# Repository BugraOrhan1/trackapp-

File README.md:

# 📡 TrackApp - RF Signal Scanner
## Eigen gebouwde Target Blue Eye alternatief
### Versie 2.0 - Juni 2026

---

## WAT IS DIT?

TrackApp is een zelfgebouwde RF (Radio Frequentie) scanner.
Hij scant het frequentiebereik 380-400 MHz.
Dat is de band waar in Nederland C2000 hulpdiensten op werken.

De scanner meet ALLEEN de signaalsterkte.
Hij decodeert NIETS - hij luistert niet mee naar gesprekken.

Op basis van de sterkte gaan LED lampjes branden.
Hoe sterker het signaal, hoe meer LEDs er branden.

Het systeem heeft een Smart Analyzer die leert welke
signalen van vaste masten komen. Die worden genegeerd.
Alleen nieuwe/wisselende signalen activeren de LEDs.

---

## HARDWARE

| Onderdeel | Type |
|-----------|------|
| Computer | Raspberry Pi Zero 2 W |
| Radio | RTL-SDR 2832 USB dongle |
| LEDs | 4x (groen/geel/oranje/rood) |
| Weerstanden | 4x 330 Ohm |
| SD kaart | 32GB Class 10 |

---

## BEDRADING

### GPIO Pin Schema (BCM)
GPIO 17 ──[330Ω]──[🟢 GROEN ]──GND
GPIO 27 ──[330Ω]──[🟡 GEEL ]──GND
GPIO 22 ──[330Ω]──[🟠 ORANJE]──GND
GPIO 23 ──[330Ω]──[🔴 ROOD ]──GND
USB ──── [RTL-SDR Dongle] ──── [Antenne]

text

### Pin Tabel

| LED | Kleur | GPIO | Fysieke Pin |
|-----|-------|------|-------------|
| Groen | 🟢 | 17 | 11 |
| Geel | 🟡 | 27 | 13 |
| Oranje | 🟠 | 22 | 15 |
| Rood | 🔴 | 23 | 16 |

---

## INSTALLATIE

### Stap 1: Raspberry Pi OS

Gebruik Raspberry Pi Imager:
- OS: Raspberry Pi OS Lite (64-bit)
- Hostname: test
- Username: test
- Enable SSH
- WiFi configureren

### Stap 2: SSH naar Pi

```bash
ssh test@test.local
Stap 3: Code downloaden
Bash

cd ~
sudo apt update
sudo apt install -y git
git clone https://github.com/BugraOrhan1/trackapp-.git
cd trackapp-/TrackApp/raspberry-pi
chmod +x install.sh
sudo ./install.sh
Stap 4: Fixes
Bash

# pyrtlsdr downgrade
sudo /opt/tetra-scanner/venv/bin/pip uninstall pyrtlsdr -y
sudo /opt/tetra-scanner/venv/bin/pip install pyrtlsdr==0.3.0

# pkg_resources patch
RTLSDR_INIT=$(find /opt/tetra-scanner/venv -name "__init__.py" -path "*/rtlsdr/*" | head -1)
sudo sed -i 's|^import pkg_resources|try:\n    import pkg_resources\nexcept ImportError:\n    import importlib.metadata as pkg_resources|' "$RTLSDR_INIT"
Stap 5: Kalibreren
Bash

sudo systemctl stop tetra-scanner
cd /opt/tetra-scanner
sudo venv/bin/python3 calibrate.py
# Pas drempels aan in config.py met de aanbevolen waarden
sudo systemctl start tetra-scanner
Stap 6: Reboot
Bash

sudo reboot
LED GEDRAG
Normaal
LED Status	Betekenis
Groen knippert kort (elke 3 sec)	Systeem leeft, geen signaal
Alles uit	Scanner gestopt of crashed
Groen vast aan	Zwak mobiel signaal
Groen + Geel	Middelmatig signaal
Groen + Geel + Oranje	Sterk signaal
Groen + Geel + Oranje + Rood	Zeer sterk signaal
Alle 4 flashen	BURST detectie
Pulserend	BEWEGING detectie
Opstart
Wat je ziet	Betekenis
Knight Rider effect	Scanner start op
2x groen knippert	Opstart compleet
Rood knippert 5x	Init fout
Rood knippert 10x	RTL-SDR niet gevonden
Foutdiagnose
Symptoom	Probleem	Oplossing
Geen heartbeat	Scanner crashed	Reboot
Rood blijft knipperen	RTL-SDR fout	Check USB
Alle LEDs altijd aan	Drempels te laag	Kalibreer
Geen LEDs ooit aan	Drempels te hoog	Kalibreer
LEDs flikkeren snel	Gain probleem	Check config
SMART ANALYZER
Hoe werkt het
Eerste 20 scans = leerperiode.
Daarna: slim filteren actief.

Detectie Types
Type	Wat
MAST	Vast basisstation (genegeerd)
MOBIEL	Wisselend signaal
BURST	Plotseling signaal
BEWEGING	Naderend signaal
Strike Systeem
7 stabiele metingen → MAST
Wisselende metingen → strikes omlaag
0 strikes → weer MOBIEL
LED Drempels (Smart mode)
dB	LED
28+	🟢 Groen
38+	🟡 + Geel
48+	🟠 + Oranje
60+	🔴 + Rood
BESTANDEN
text

/opt/tetra-scanner/
├── scanner.py          ← Hoofdprogramma
├── config.py           ← Instellingen
├── signal_analyzer.py  ← RTL-SDR + FFT
├── smart_analyzer.py   ← Slim brein
├── led_controller.py   ← LED + heartbeat
├── web.py              ← Webpagina
├── calibrate.py        ← Kalibratie tool
├── data/               ← CSV + masten
├── logs/               ← Log bestanden
└── venv/               ← Python env
SERVICES
Service	Functie
tetra-scanner	De scanner
trackapp-web	Webpagina
wifi-dual	Hotspot + WiFi
tetra-health.timer	Health check (60s)
watchdog	Hardware watchdog
tailscaled	Tailscale VPN
Commando's
Bash

# Status
sudo systemctl status tetra-scanner

# Logs
sudo journalctl -u tetra-scanner -f

# Restart
sudo systemctl restart tetra-scanner

# Stop
sudo systemctl stop tetra-scanner
WIFI EN HOTSPOT
Dual Mode
Pi maakt twee interfaces:

wlan0 = thuis WiFi (internet)
uap0 = TrackApp hotspot
Beide werken tegelijk.

TrackApp Hotspot
Setting	Value
SSID	TrackApp
Password	TrackApp2026
IP	192.168.50.1
Channel	6
Webpagina
Thuis: http://test.local:8080
Hotspot: http://192.168.50.1:8080
Tailscale: http://100.107.246.20:8080
TAILSCALE
Bash

# Setup eenmalig
sudo tailscale up --ssh

# IP opvragen
tailscale ip -4

# Status
tailscale status
Werkt alleen met internet.

HANDIGE COMMANDO'S
Logs bekijken
Bash

sudo journalctl -u tetra-scanner -f
sudo journalctl -u tetra-scanner -n 50
sudo journalctl -u tetra-scanner --since '30 min ago'
Drempels aanpassen
Bash

sudo sed -i 's/^THRESHOLD_GREEN.*=.*/THRESHOLD_GREEN = 47.2/' /opt/tetra-scanner/config.py
sudo systemctl restart tetra-scanner
Handmatig testen
Bash

sudo systemctl stop tetra-scanner
cd /opt/tetra-scanner
sudo env TERM=xterm ./venv/bin/python3 scanner.py
# Ctrl+C om te stoppen
sudo systemctl start tetra-scanner
CSV data bekijken
Bash

ls -t /opt/tetra-scanner/data/signal_data_*.csv | head -5
tail -20 $(ls -t /opt/tetra-scanner/data/signal_data_*.csv | head -1)
Bekende masten
Bash

cat /opt/tetra-scanner/data/known_masts.json
WiFi checks
Bash

iwgetid -r
ip -4 addr show
sudo iw dev uap0 station dump
Updates naar GitHub
Bash

cd ~/trackapp-/TrackApp/raspberry-pi
sudo cp /opt/tetra-scanner/*.py .
sudo chown -R test:test .
cd ~/trackapp-
git add .
git commit -m "Update: beschrijving"
git push
PROBLEMEN OPLOSSEN
Scanner start niet
Bash

sudo systemctl status tetra-scanner
sudo journalctl -u tetra-scanner -n 50
sudo systemctl restart tetra-scanner
RTL-SDR niet gevonden
Bash

lsusb | grep -i rtl
sudo reboot
pyrtlsdr error
Bash

/opt/tetra-scanner/venv/bin/python3 -c "import rtlsdr; print('OK')"
sudo /opt/tetra-scanner/venv/bin/pip install pyrtlsdr==0.3.0
Alle LEDs branden
Oorzaak: drempels te laag. Kalibreer opnieuw.

Geen LEDs ooit aan
Oorzaak: drempels te hoog OF geen signaal. Test met:

Bash

sudo systemctl stop tetra-scanner
python3 << 'TESTEOF'
import RPi.GPIO as GPIO
import time
GPIO.setmode(GPIO.BCM)
for pin in [17, 27, 22, 23]:
    GPIO.setup(pin, GPIO.OUT)
    GPIO.output(pin, GPIO.HIGH)
    time.sleep(1)
    GPIO.output(pin, GPIO.LOW)
GPIO.cleanup()
TESTEOF
sudo systemctl start tetra-scanner
Pi reageert niet
Wacht 2 minuten (watchdog herstart)
Stroom eraf, 10 sec wachten, weer erop
Als niets: SD kaart check
SD vol
Bash

df -h
sudo rm /opt/tetra-scanner/data/signal_data_2026050*.csv
sudo journalctl --vacuum-time=3d
TECHNISCHE DETAILS
Scan instellingen
Bereik: 380-400 MHz
Stap: 25 kHz
Frequenties: 801
Sample rate: 1.024 MHz
Samples: 65536
Smart Analyzer
Parameter	Waarde
Stable strikes nodig	7
Max strikes	25
History length	60
Std stable threshold	2.5 dB
Movement threshold	4.0 dB
Location overlap	30%
Learning scans	20
LED Drempels Smart Mode
text

28+ dB → Groen
38+ dB → Geel
48+ dB → Oranje
60+ dB → Rood
CONFIG.PY INSTELLINGEN
Python

FREQ_START_MHZ = 380.0
FREQ_END_MHZ = 400.0
FREQ_STEP_MHZ = 0.025
SAMPLE_RATE = 1024000
GAIN = 35.0
PPM_CORRECTION = 0

LED_GREEN = 17
LED_YELLOW = 27
LED_ORANGE = 22
LED_RED = 23

THRESHOLD_GREEN = 47.2
THRESHOLD_YELLOW = 53.2
THRESHOLD_ORANGE = 61.2
THRESHOLD_RED = 71.2

SCAN_INTERVAL = 0.5
SHOW_TERMINAL_OUTPUT = False
LOG_LEVEL = "INFO"
GEBRUIK IN DE AUTO
Setup
Pi op 5V USB lader
RTL-SDR in USB DATA poort
Antenne opzetten
2-3 minuten wachten
Wat je ziet
Knight Rider = opstarten
2x groen flash = klaar
Groen knippert = alles werkt
LEDs branden = actief signaal
Tips
Antenne: externe magneetvoet op dak = 10x beter
Positie: niet achter metaal
Kalibreer op locatie waar je het meest bent
Gain 35 dB is meestal goed
Stroom: goede 5V voeding
LOKALE WIJZIGINGEN LOG
#	Wijziging	Bestand
1	Vaste Gain (35.0)	config.py
2	PPM correctie fix	signal_analyzer.py
3	pyrtlsdr 0.3.0	venv
4	pkg_resources patch	rtlsdr/init.py
5	Smart Analyzer v3.0	smart_analyzer.py
6	Ultra LED Controller	led_controller.py
7	Dual Mode WiFi	wifi-dual.sh
8	Web Interface	web.py
9	Health Check	tetra-health
10	Hardware Watchdog	/etc/watchdog.conf
11	Tailscale	systeem
12	Drempels gekalibreerd	config.py
13	DVB-T blacklist	modprobe.d
14	GPIO pinnen	config.py
VERSIE INFO
Versie: 2.0
Datum: Juni 2026
Maker: BugraOrhan1
Hardware: Raspberry Pi Zero 2 W + RTL-SDR 2832
OS: Raspberry Pi OS Debian Trixie 64-bit
Python: 3.13
JURIDISCHE WAARSCHUWING
Het afluisteren van hulpdiensten (C2000/TETRA) is in
Nederland illegaal volgens de Telecommunicatiewet
(Art. 139c Wetboek van Strafrecht).

Dit project is ALLEEN voor educatieve doeleinden.
Het meet ALLEEN signaalsterkte.
Het decodeert GEEN communicatie.
Het luistert NIET mee met gesprekken.

Gebruik conform lokale wetgeving.
De maker is niet verantwoordelijk voor misbruik.

LINKS
Repository: https://github.com/BugraOrhan1/trackapp-
Raspberry Pi Imager: https://www.raspberrypi.com/software/
Win32 Disk Imager: https://sourceforge.net/projects/win32diskimager/
Tailscale: https://tailscale.com
RTL-SDR: https://www.rtl-sdr.com
EINDE README

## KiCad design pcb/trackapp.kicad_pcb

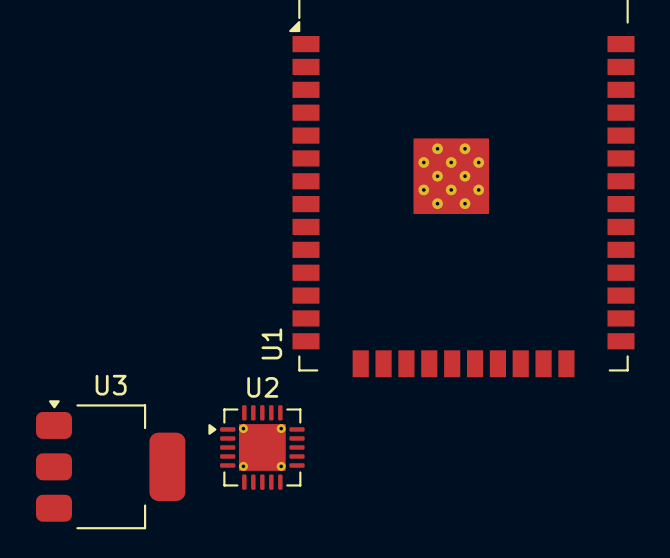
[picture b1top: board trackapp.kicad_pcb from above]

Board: 2 copper layers, 3 parts (0 on the bottom side), 2 nets, no tracks yet.

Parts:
U1: ESP32-WROOM-32
U2: Si4463; QFN-20-1EP_4x4mm_P0.5mm_EP2.6x2.6mm_ThermalVias
U3: AMS1117-3.3; SOT-223-3_TabPin2

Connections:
unnamed: U1.1 (GND), U1.15 (GND), U1.38 (GND), U1.39 (GND)
unnamed: U2.18 (GND), U2.21 (GND)

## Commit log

2026-03-23 first upload raspberry scanner + web app
2026-03-23 Auto Bluetooth paired-device connect and reconnect
2026-03-23 Fix netlify.toml paths for deployment
2026-03-23 Add environment variables template
2026-03-23 Add Neon database setup and verification guide
2026-03-23 Add complete .env template and SQL schema ready to paste
2026-03-23 Improve JWT_SECRET documentation with security requirements
2026-03-23 Fix deprecated mobile-web-app meta tag
2026-03-23 Add detailed error logging and health check endpoint
2026-03-23 TEMP: Disable authentication - demo mode enabled
2026-03-23 Add comprehensive Raspberry Pi Bluetooth communication setup guide
2026-03-23 Fix bluetoothctl pairing commands - clarify interactive menu vs terminal
2026-03-23 Add quick-start scripts for easy project setup
2026-03-23 Add all-in-one Raspberry Pi setup script
2026-03-23 Fix setuptools version from 81.0.2 to 80.10.2 (81.0.2 doesn't exist)
2026-03-24 Improve reliability: configurable auth mode, safer API requests, hardened Pi setup
2026-03-25 Repo cleanup: merge docs, remove redundant files, simplify run workflow
2026-03-25 Add temporary local API/database mode to run without Netlify
2026-03-25 Tune scanner: adaptive background EMA and explicit green level
2026-03-25 Fix scanner default run: fallback argparse defaults for systemd startup
2026-03-25 Fix Bluetooth auto-bind for new bluetoothctl syntax
2026-03-25 Fix rfcomm lifecycle: bind as root in systemd and persist BT target MAC
2026-03-25 Improve drive-by detection and add pre-alert diagnostics
2026-03-26 BLE + webapp RF orb realtime scaling and decay
2026-03-26 Add iOS cloud build path and signal-mode BLE app updates
2026-03-26 Fix iOS cloud workflow cache and artifact paths
2026-03-26 Harden setup-node cache path for iOS workflow
2026-03-26 Add TypeScript for Capacitor TS config in iOS CI
2026-03-26 Fix Capacitor webDir and CI web asset sync for iOS build
2026-03-26 Add optional TestFlight upload flow and docs
2026-03-30 backup
2026-03-31 TrackApp BLE: eerste commit na opschoning
2026-04-03 TrackApp: BLE JSON flow + RTL scanner + webapp sync + README updates
2026-04-03 Restructure TrackApp into four app folders
2026-04-03 page fix
2026-04-03 Fix GitHub Pages deployment via gh-pages branch
2026-04-03 Remove Node20 gh-pages action from deploy workflow
2026-04-03 0.0.91
2026-04-03 0.0.92
2026-04-03 0.0.93
2026-04-03 Deploy webapp to GitHub Pages
2026-04-06 Show app directly without login
2026-04-06 Start app directly without login
2026-04-06 Clarify Pi BLE unsupported on iPhone browsers
2026-04-10 update for beta
2026-04-10 beta update v1.1
2026-04-10 beta v3
2026-04-10 beta v4
2026-04-10 beta v4.1
2026-04-10 beta v 5
2026-04-10 Add iOS IPA GitHub Actions workflow
2026-04-10 Move iOS workflow to repo root
2026-04-10 Harden iOS workflow secret checks
2026-04-10 Use production environment for iOS workflow
2026-04-10 Use TrackApp environment for iOS workflow
2026-04-10 Fix EAS config validation
2026-04-10 Link EAS project and enable remote versioning
2026-04-13 Fix iOS build plist and EAS env config
2026-04-13 Fix iOS build dependencies and EAS ignores
2026-04-13 Fix corrupt Expo PNG assets
2026-04-13 Tighten EAS node_modules ignore patterns
2026-04-13 Suppress Expo Go warning in iOS workflow
2026-04-13 Suppress Expo Go warning in EAS build profile
2026-04-13 Fix Expo 55 iOS build config
2026-04-13 Fix Expo 55 build blockers
2026-04-13 Add GitHub Actions build
2026-04-13 Fix: fresh package-lock.json
2026-04-13 Ignore root ipa artifacts
2026-04-13 "Switch to local Mac build (no EAS queue)"
2026-04-13 Fix: pass EXPO_TOKEN to all build steps
2026-04-13 Fix: add environment TrackApp to access secrets
2026-04-13 Fix iOS map provider for Apple Maps
2026-04-13 Remove unused Babel module resolver
2026-04-13 Fix babel-preset-expo and ws bundling
2026-04-13 Fix RevenueCat Xcode compatibility
2026-04-13 Remove unused iOS Google Maps env key
2026-04-15 Fix EAS npm ci exit handler bug
2026-04-15 Fix: clear EAS cache for iOS build
2026-04-15 Fix: update expo-av for SDK 55
2026-04-15 Fix: patch expo-av for Expo SDK 55
2026-04-15 Fix: opt GitHub Actions into Node 24
2026-04-15 Fix: upgrade GitHub Actions to Node 24 majors
2026-04-15 Fix: align worklets version for iOS builds
2026-04-15 Sync package-lock.json
2026-05-09 Add Raspberry Pi LED scanner control
2026-05-09 Update Raspberry Pi boot flow and configs
2026-05-09 Fix Raspberry Pi install with venv
2026-05-09 Use break-system-packages on Raspberry Pi
2026-05-09 Make Raspberry Pi install self-starting
2026-05-31 Raspberry Pi: unified distance LED indicator, one-command installer and journald logging
2026-05-31 Fix: make ble_server.py tolerant to pydbus signal signature differences
2026-05-31 Improve scanner: hysteresis/persistence for LEDs; make BLE optional in start.sh; docs
2026-05-31 Fix: robustly obtain BlueZ adapter proxy across pydbus versions
2026-05-31 Fallback: demo LED mode when rtlsdr not available (keeps service alive for wiring tests)
2026-05-31 rTLSDR import: try rtlsdr, fallback to pyrtlsdr; catch import-time errors
2026-05-31 Replace Raspberry Pi tools with TETRA scanner
2026-06-02 Working version - Smart Analyzer + Dual mode + Web interface
2026-06-02 Complete README v2.0 - alle docs, commandos, troubleshooting
2026-06-02 Smart Analyzer v4.0 - Hulpdiensten focus, burst detection, false positive filter, optimized config
2026-06-02 v4.3 - Special effects uit, alleen stabiele LED levels
2026-06-06 v5.2 - PERFECT: Baseline percentiel, sticky masten, geen vals alarm
